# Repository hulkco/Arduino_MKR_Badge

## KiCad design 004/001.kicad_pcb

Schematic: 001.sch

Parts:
D1, D2, D3, D4, D5, D6, D7, D8, D9, D10: LED_ALT; SunLed_PLCC_Reverse-2
J1, J2: CONN_01X08; PinSocket_1x08_P2.54mm_Vertical_SMD_Pin1Left
R1, R2, R3, R4, R5, R6, R7, R8, R9, R10: R; R_1206_3216Metric_Pad1.39x1.80mm_HandSolder
U1: 2019.All.Mask.02; 2019.2.All.B.Mask
U2: 2019.All.Mask.03; 2019.2.All
U3: Arduino.SilkS
U4: Edge.Back.Only.SilkS.02
U5: Edge.Only.SilkS.02
U6: Fig.04.Cu.Mask
U7: Fig.05.Cu.Mask
U8: Fig.06.Cu.Mask
U9: Holder.B.Cu.Mask.01
U10: Holder.Cu.Mask.01
U11: logo.B.Mask.Der.01
U12: logo.B.Mask.Izq.01
U13: logo.F.Mask.Der.01
U14: logo.F.Mask.Izq.01
U15: MKR_Family; MKR_Family_SMD

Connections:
+3V3: J2.8, U15.26
/A1: J1.2, U15.3
/A2: J1.3, U15.4
/A3: J1.4, U15.5
/A4: J1.5, U15.6
/A5: J1.6, U15.7
/A6: J1.7, U15.8
/D0: D1.2 (A), U15.9
/D1: D2.2 (A), U15.10
/D6: D7.2 (A), U15.15
/D7: D8.2 (A), U15.16
/D8-MOSI: D9.2 (A), J2.7, U15.17
/D9-SCK: D10.2 (A), J2.6, U15.18
/D10-MISO: J2.5, U15.19
/D11-SDA: J2.4, U15.20
/D12-SCL: J2.3, U15.21
/D13->RX: J2.2, U15.22
/D14<-TX: J2.1, U15.23
/DAC0-A0: J1.1, U15.2
/~D2: D3.2 (A), U15.11
/~D3: D4.2 (A), U15.12
/~D4: D5.2 (A), U15.13
/~D5: D6.2 (A), U15.14
GND: J1.8, R1.2, R2.2, R3.2, R4.2, R5.2, R6.2, R7.2, R8.2, R9.2, R10.2, U15.25
unnamed: D1.1 (K), R1.1
unnamed: D2.1 (K), R2.1
unnamed: D3.1 (K), R3.1
unnamed: D4.1 (K), R4.1
unnamed: D5.1 (K), R5.1
unnamed: D6.1 (K), R6.1
unnamed: D7.1 (K), R7.1
unnamed: D8.1 (K), R8.1
unnamed: D9.1 (K), R9.1
unnamed: D10.1 (K), R10.1

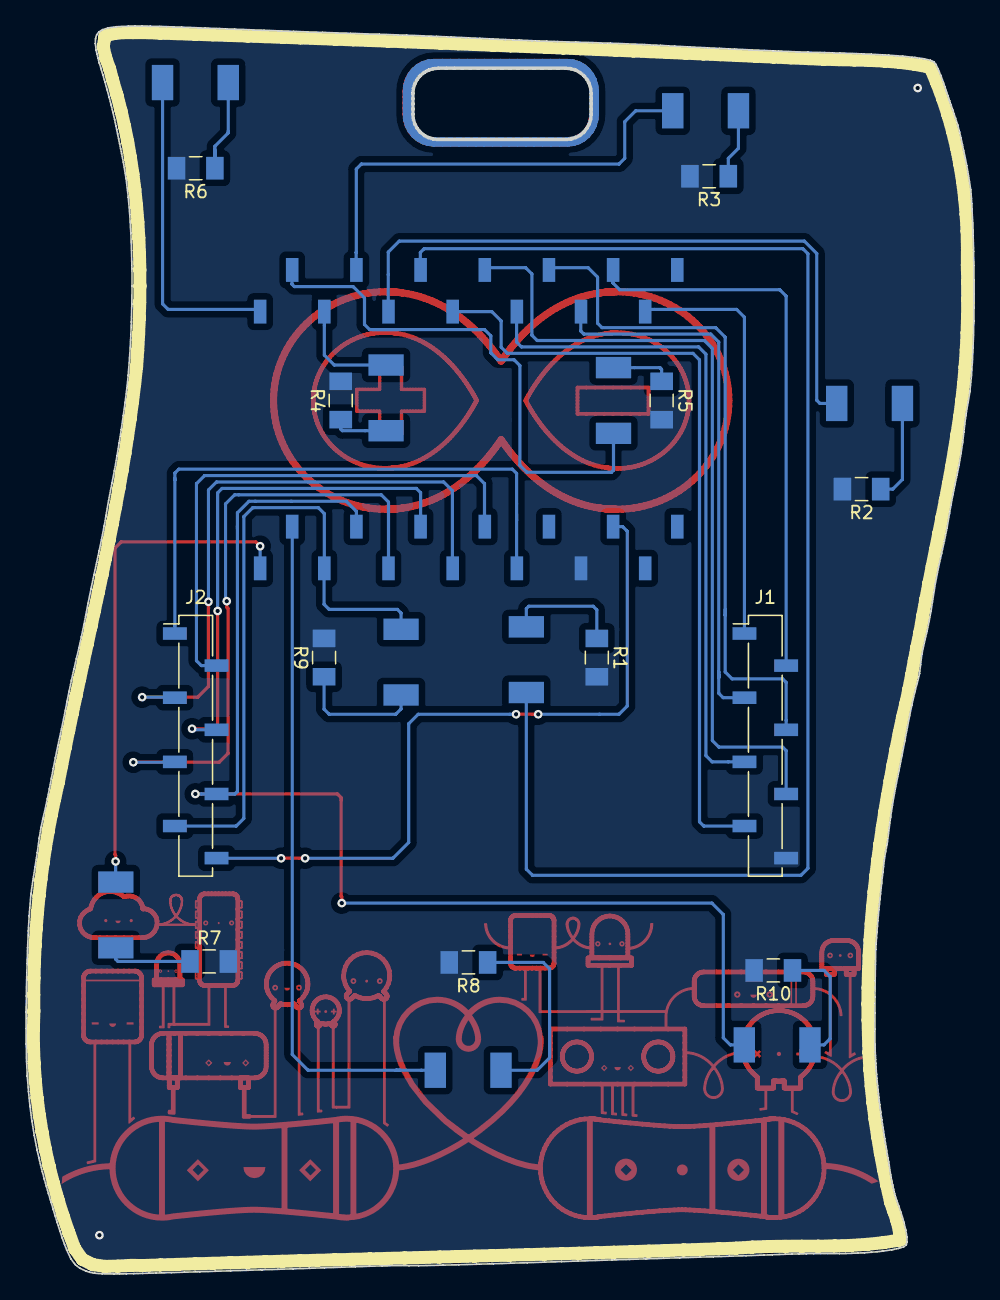
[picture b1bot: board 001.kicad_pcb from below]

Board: 2 copper layers, 74.9 x 98.6 mm, 37 parts (27 on the bottom side), 34 nets.

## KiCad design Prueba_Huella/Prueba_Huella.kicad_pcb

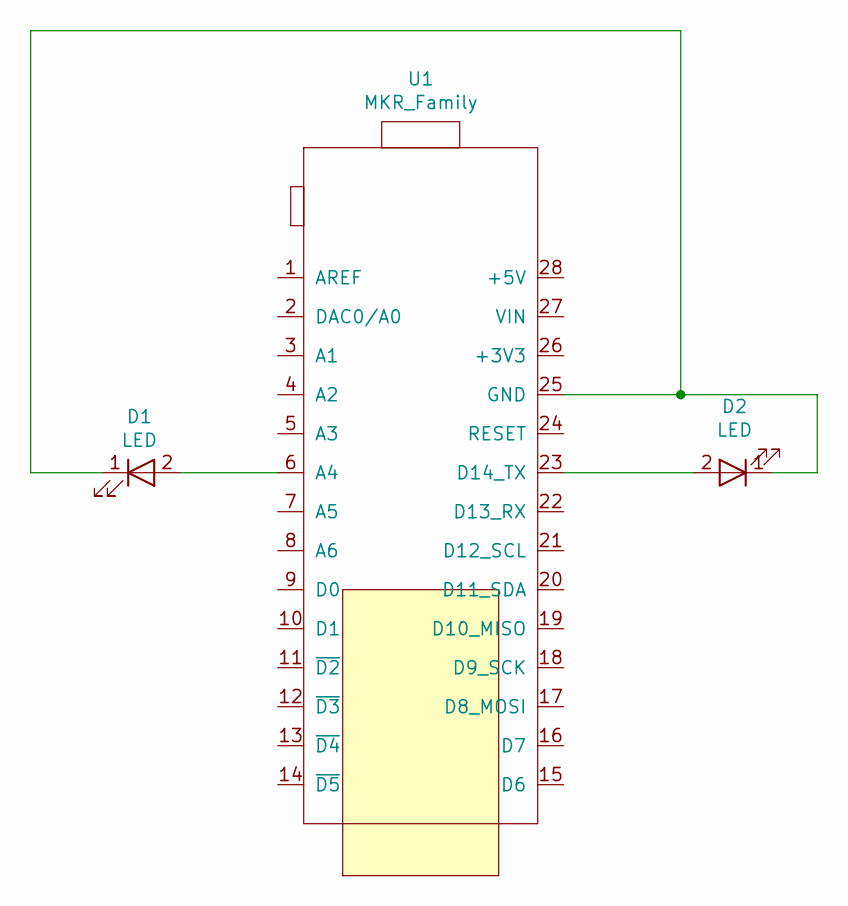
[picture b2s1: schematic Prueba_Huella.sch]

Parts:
D1, D2: LED; LED_0805_2012Metric_Pad1.12x1.40mm_HandSolder
U1: MKR_Family; MKR_Family_SMD

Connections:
unnamed: D1.1 (K), D2.1 (K), U1.25 (GND)
unnamed: D1.2 (A), U1.6 (A4)
unnamed: D2.2 (A), U1.23 (D14_TX)

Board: 2 copper layers, 3 parts (0 on the bottom side), 3 nets, no tracks yet.

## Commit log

2018-12-07 Firts Upload
2018-12-10 Add HoleBig
2019-01-22 Update Edge
2019-01-31 Auto stash before merge of "master" and "origin/master"
2019-02-02 Update H
2019-02-05 Add new shapes
2019-02-06 Add Firma to MKR Badge
2019-02-06 Updates Mask
2019-02-07 Add Footprint MKR Family
2019-02-08 Updates de Huellas
2019-03-06 Rooteo
    Se rooteo la carpeta 004 coin dos versiones una a una capa y la otra en las dos, saludos! @antonio_raptors
